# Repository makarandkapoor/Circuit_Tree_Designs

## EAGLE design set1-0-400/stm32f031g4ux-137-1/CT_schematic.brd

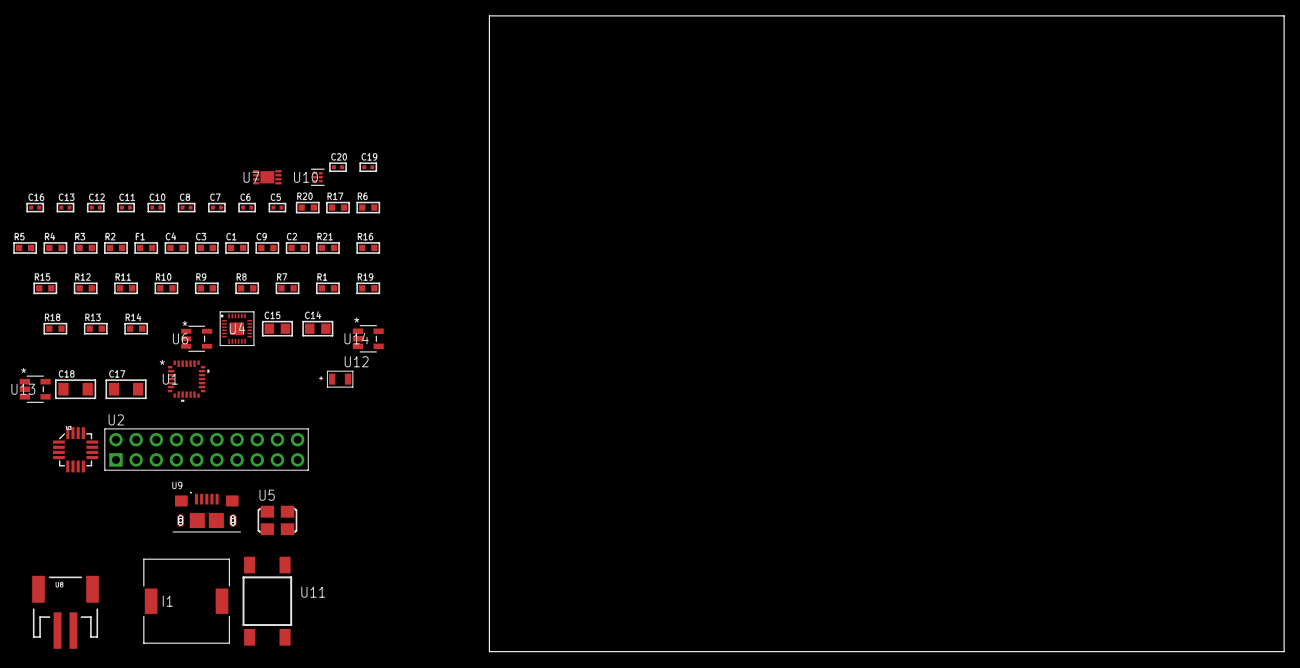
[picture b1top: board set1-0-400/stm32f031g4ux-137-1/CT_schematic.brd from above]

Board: 2 copper layers, 57 parts (0 on the bottom side), 34 nets, no tracks yet.

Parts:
C1: 1e-07; C0603
C2: 4.7e-06; C0603
C3: 1e-08; C0603
C4: 1e-06; C0603
C5, C10, C11, C16: 1e-07; C0402
C6, C7, C8, C12, C13, C19, C20: 1e-08; C0402
C9: 4.7e-07; C0603
C14, C15: 1e-05; C0805
C17, C18: 1e-05; C1206
F1: 240.0; L0603
I1: 2.5e-06; DR1040
R1, R7, R8, R9, R10, R11, R12, R15, R16, R21: 10000.0; R0603
R2: 1000.0; R0603
R3: 1600.5; R0603
R4: 4700.0; R0603
R5, R6: 2200.0; R0603
R13: 220000.0; R0603
R14: 1000000.0; R0603
R17: 9100.0; R0603
R18: 680000.0; R0603
R19: 120000.0; R0603
R20: 2000.0; R0603
U1: stm32f031g4u7; UFQFPN28
U2: TST-110-05-T-D-RA
U3: l3g4200d; LGA-16
U4: MPU-9250; QFN24_2
U5: ASFL1-25MHZ-NCS; ASFL1
U6: ltc3406es5; TSOT-23-5
U7: MCP73831T-2ACI/MC; DFN8_2X3MC
U8: S2B-PH-SM4-TB(LF)(SN); JST-2-SMD
U9: 10118193-0001LF; FCI_10118193-0001LF
U10: TPS3895ADRYR; SON-6
U11: 4-1437565-2; SW_4-1437565-2
U12: Q65110A2395; LGM67K-G1J2-24-Z
U13, U14: nc7sz125m5x; NC7SZ125M5X

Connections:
CLK_U1_2: U1.2, U5.3
GND: C1.2, C2.2, C3.2, C4.2, C5.2, C6.2, C7.2, C8.2, C10.2, C11.2, C12.2, C13.2, C14.2, C15.1, C15.2, C16.2, C17.2, C18.2, C19.2, C20.2, R2.2, R7.2, R9.1, R9.2, R12.2, R13.2, R17.2, R19.2, R20.2, U1.16, U2.4, U2.6, U2.8, U2.10, U2.12, U2.14, U2.16, U2.18, U2.20, U3.8, U3.9, U3.10, U3.11, U3.12, U3.13, U4.18, U4.20, U4.25, U5.2, U6.2, U7.6, U7.9, U8.2, U9.5, U9.6, U9.7, U9.8, U9.9, U10.2, U12.C, U13.2, U13.3, U14.1, U14.3
INPUT_USBPOWER_5V: C17.1, R21.2, U7.1, U7.2, U9.1
NET_U1_1: R7.1, U1.1
NET_U1_4: R4.1, U1.4, U14.4
NET_U1_5: C3.1, C4.1, F1.1, U1.5
NET_U1_19: R5.1, U1.19, U4.23
NET_U1_20: R6.1, U1.20, U4.24
NET_U1_27: R3.1, U1.27, U12.A
NET_U1_28: R1.1, U1.28, U11.3, U11.4
NET_U3_14: C8.1, C9.1, U3.14
NET_U4_9: R12.1, U4.9
NET_U4_10: C10.1, U4.10
NET_U4_22: R11.1, U4.22
NET_U6_3: I1.1, U6.3
NET_U6_5: R13.1, R14.1, U6.5
NET_U6_ATNET_3: I1.2, R14.2
NET_U7_5: R21.1, U7.5
NET_U7_8: R20.1, U7.8
NET_U10_1: R16.1, R17.1, U10.1
NET_U10_3: R18.2, R19.1, U10.3
NET_U10_4: R15.1, U10.4, U13.4, U14.2
NET_U11_1: R2.1, U11.1, U11.2
PROC_GPIO_TO_U4_FSYNC: U1.6, U4.11
PROC_GPIO_TO_U4_INT_B: U1.3, U4.12
PROC_SPI1_MISO: U1.12, U3.4
PROC_SPI1_MOSI: U1.13, U3.3
PROC_SPI1_NSS: R10.1, U1.10, U3.5
PROC_SPI1_SCK: U1.11, U3.2
PROC_SYS_SWCLK: U1.22, U2.9
PROC_SYS_SWDIO: U1.21, U2.7
RST_OUT_U2_SRESET_B: R8.1, U2.15, U13.1
VCC_S1_3V7: C14.1, C18.1, U6.4, U7.3, U7.4, U8.1
VCC_TIER1_3V3: C1.1, C2.1, C5.1, C6.1, C7.1, C11.1, C12.1, C13.1, C15.2, C16.1, C19.1, C20.1, F1.2, I1.2, R1.2, R3.2, R4.2, R5.2, R6.2, R8.2, R10.2, R11.2, R14.2, R15.2, R16.2, R18.1, U1.17, U2.1, U3.1, U3.15, U3.16, U4.1, U4.8, U4.13, U5.4, U10.6, U13.5, U14.5

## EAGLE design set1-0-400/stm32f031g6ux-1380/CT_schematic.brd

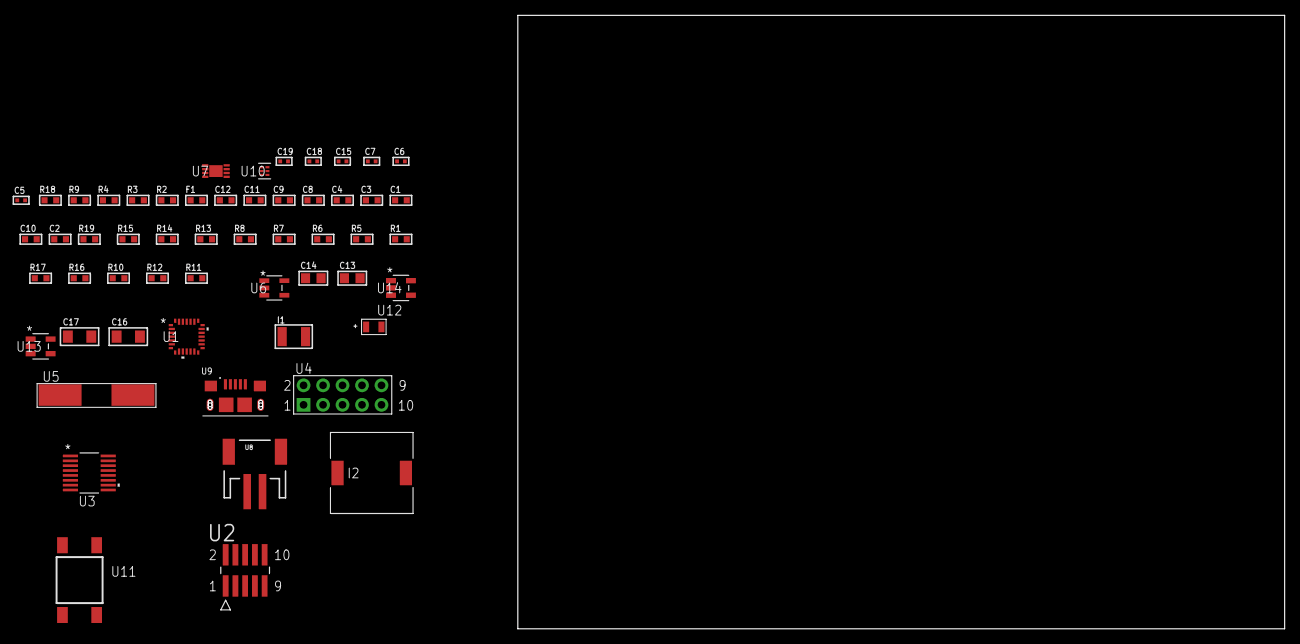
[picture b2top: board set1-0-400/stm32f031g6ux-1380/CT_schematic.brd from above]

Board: 2 copper layers, 55 parts (0 on the bottom side), 37 nets, no tracks yet.

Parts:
C1: 1e-07; C0603
C2: 4.7e-06; C0603
C3: 1e-08; C0603
C4, C8, C9, C11, C12: 1e-06; C0603
C5, C6: 1e-11; C0402
C7, C15: 1e-07; C0402
C10: 2.2e-07; C0603
C13, C14: 1e-05; C0805
C16, C17: 1e-05; C1206
C18, C19: 1e-08; C0402
F1: 240.0; L0603
I1: 1e-05; L1210
I2: 7e-06; DR1040
R1, R5, R6, R7, R8, R13, R14, R19: 10000.0; R0603
R2: 1000.0; R0603
R3: 1270.0; R0603
R4: 4700.0; R0603
R9: 5.0; R0603
R10: 100000.0; R0603
R11: 309473.68421053; R0603
R12: 1000000.0; R0603
R15: 18000.0; R0603
R16: 470000.0; R0603
R17: 120000.0; R0603
R18: 2000.0; R0603
U1: stm32f031g6u7; UFQFPN28
U2: FTSH-105-01-L-DV-K; SAMTEC_FTSH-105-01-L-DV-K
U3: LTC2804CGN-1#PBF; SSOP-16
U4: HTSS-105-01-G-D
U5: ABLS-25.000MHZ-B2F-T
U6: ltc3406es5; TSOT-23-5
U7: MCP73831T-2ACI/MC; DFN8_2X3MC
U8: S2B-PH-SM4-TB(LF)(SN); JST-2-SMD
U9: 10118193-0001LF; FCI_10118193-0001LF
U10: TPS3895ADRYR; SON-6
U11: 4-1437565-2; SW_4-1437565-2
U12: Q65110A2395; LGM67K-G1J2-24-Z
U13, U14: nc7sz125m5x; NC7SZ125M5X

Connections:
CLK_CRYSTAL_U1_2: C5.1, U1.2, U5.1
CLK_CRYSTAL_U1_3: C6.1, U1.3, U5.2
GND: C1.2, C2.2, C3.2, C4.2, C5.2, C6.2, C7.2, C8.2, C9.2, C11.2, C12.2, C13.2, C14.1, C14.2, C15.2, C16.2, C17.2, C18.2, C19.2, R2.2, R5.2, R9.2, R11.2, R15.2, R17.2, R18.2, U1.16, U2.3, U2.5, U3.8, U4.9, U6.2, U7.6, U7.9, U8.2, U9.5, U9.6, U9.7, U9.8, U9.9, U10.2, U12.C, U13.2, U13.3, U14.1, U14.3
INPUT_USBPOWER_5V: C16.1, R19.2, U7.1, U7.2, U9.1
NET_U1_1: R5.1, U1.1
NET_U1_4: R4.1, U1.4, U14.4
NET_U1_5: C3.1, C4.1, F1.1, U1.5
NET_U1_27: R3.1, U1.27, U12.A
NET_U1_28: R1.1, U1.28, U11.3, U11.4
NET_U2_9: R9.1, U2.9
NET_U3_6: C8.1, U3.6
NET_U3_7: C10.1, I1.2, U3.7
NET_U3_9: C9.1, U3.9
NET_U3_10: C10.2, U3.10
NET_U3_11: R10.1, U3.11
NET_U4_3: U3.1, U4.3
NET_U4_4: U3.2, U4.4
NET_U4_5: U3.3, U4.5
NET_U4_6: U3.4, U4.6
NET_U6_3: I2.1, U6.3
NET_U6_5: R11.1, R12.1, U6.5
NET_U6_ATNET_3: I2.2, R12.2
NET_U7_5: R19.1, U7.5
NET_U7_8: R18.1, U7.8
NET_U10_1: R14.1, R15.1, U10.1
NET_U10_3: R16.2, R17.1, U10.3
NET_U10_4: R13.1, U10.4, U13.4, U14.2
NET_U11_1: R2.1, U11.1, U11.2
PROC_SYS_SWCLK: R7.1, U1.22, U2.4
PROC_SYS_SWDIO: R8.1, U1.21, U2.2
PROC_USART1_CTS: U1.6, U3.13
PROC_USART1_RTS: U1.7, U3.15
PROC_USART1_RX: U1.9, U3.16
PROC_USART1_TX: U1.8, U3.14
RST_OUT_U2_JTAG_RST_B: R6.1, U2.10, U13.1
VCC_S1_3V7: C13.1, C17.1, U6.4, U7.3, U7.4, U8.1
VCC_TIER1_2V5: C1.1, C2.1, C7.1, C11.1, C12.1, C14.2, C15.1, C18.1, C19.1, F1.2, I1.1, I2.2, R1.2, R3.2, R4.2, R6.2, R7.2, R8.2, R10.2, R12.2, R13.2, R14.2, R16.1, U1.17, U2.1, U3.5, U3.12, U10.6, U13.5, U14.5

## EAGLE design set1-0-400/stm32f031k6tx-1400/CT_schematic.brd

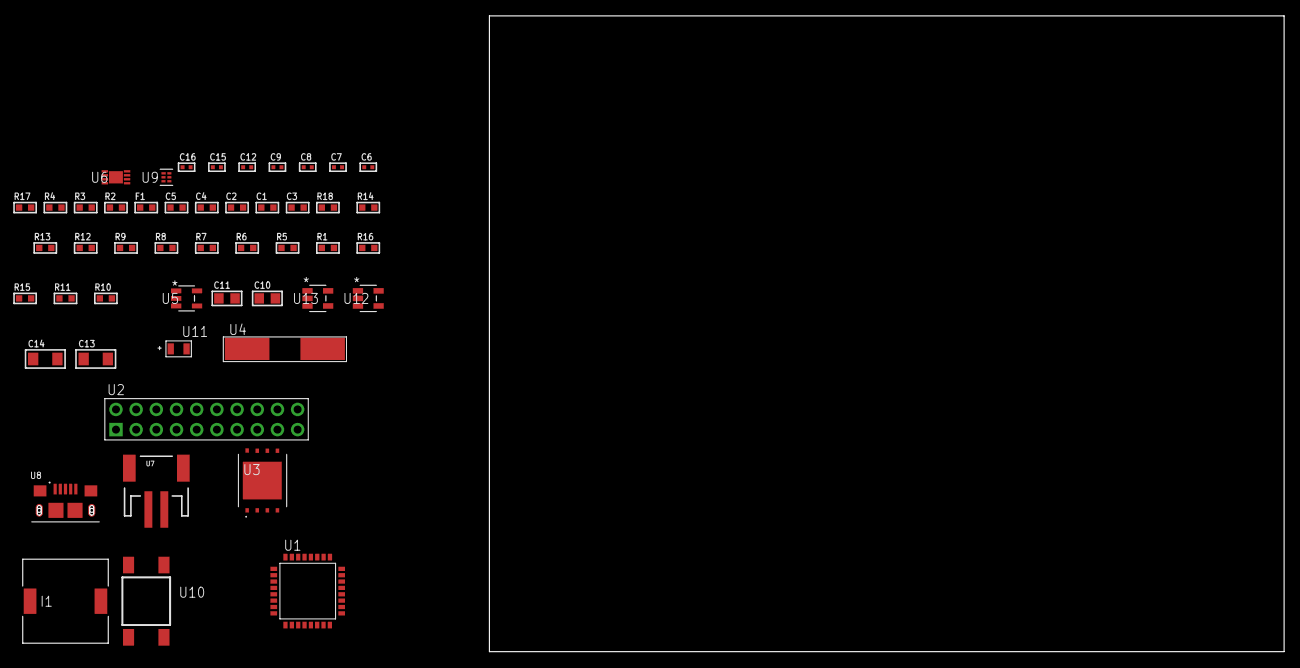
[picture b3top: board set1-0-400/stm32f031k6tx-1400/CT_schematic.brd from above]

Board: 2 copper layers, 156.9 x 80.0 mm, 49 parts (0 on the bottom side), 29 nets, no tracks yet.

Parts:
C1, C2: 1e-07; C0603
C3: 4.7e-06; C0603
C4: 1e-08; C0603
C5: 1e-06; C0603
C6, C7: 1e-11; C0402
C8, C12: 1e-07; C0402
C9, C15, C16: 1e-08; C0402
C10, C11: 1e-05; C0805
C13, C14: 1e-05; C1206
F1: 240.0; L0603
I1: 7e-06; DR1040
R1, R5, R6, R7, R8, R9, R12, R13, R18: 10000.0; R0603
R2: 1000.0; R0603
R3: 1270.0; R0603
R4: 4700.0; R0603
R10: 309473.68421053; R0603
R11: 1000000.0; R0603
R14: 18000.0; R0603
R15: 470000.0; R0603
R16: 120000.0; R0603
R17: 2000.0; R0603
U1: stm32f031k6t6; LQFP32
U2: TST-110-05-T-D-RA
U3: S25FL128SDPNFI001; WNG008
U4: ABLS-25.000MHZ-B2F-T
U5: ltc3406es5; TSOT-23-5
U6: MCP73831T-2ACI/MC; DFN8_2X3MC
U7: S2B-PH-SM4-TB(LF)(SN); JST-2-SMD
U8: 10118193-0001LF; FCI_10118193-0001LF
U9: TPS3895ADRYR; SON-6
U10: 4-1437565-2; SW_4-1437565-2
U11: Q65110A2395; LGM67K-G1J2-24-Z
U12, U13: nc7sz125m5x; NC7SZ125M5X

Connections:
CLK_CRYSTAL_U1_2: C6.1, U1.2, U4.1
CLK_CRYSTAL_U1_3: C7.1, U1.3, U4.2
GND: C1.2, C2.2, C3.2, C4.2, C5.2, C6.2, C7.2, C8.2, C9.2, C10.2, C11.1, C11.2, C12.2, C13.2, C14.2, C15.2, C16.2, R2.2, R5.2, R10.2, R14.2, R16.2, R17.2, U1.16, U1.32, U2.4, U2.6, U2.8, U2.10, U2.12, U2.14, U2.16, U2.18, U2.20, U3.4, U3.PAD, U5.2, U6.6, U6.9, U7.2, U8.5, U8.6, U8.7, U8.8, U8.9, U9.2, U11.C, U12.2, U12.3, U13.1, U13.3
INPUT_USBPOWER_5V: C13.1, R18.2, U6.1, U6.2, U8.1
NET_U1_4: R4.1, U1.4, U13.4
NET_U1_5: C4.1, C5.1, F1.1, U1.5
NET_U1_29: R3.1, U1.29, U11.A
NET_U1_30: R1.1, U1.30, U10.3, U10.4
NET_U1_31: R5.1, U1.31
NET_U3_3: R7.1, U3.3
NET_U3_7: R9.1, U3.7
NET_U5_3: I1.1, U5.3
NET_U5_5: R10.1, R11.1, U5.5
NET_U5_ATNET_3: I1.2, R11.2
NET_U6_5: R18.1, U6.5
NET_U6_8: R17.1, U6.8
NET_U9_1: R13.1, R14.1, U9.1
NET_U9_3: R15.2, R16.1, U9.3
NET_U9_4: R12.1, U9.4, U12.4, U13.2
NET_U10_1: R2.1, U10.1, U10.2
PROC_SPI1_MISO: U1.12, U3.2
PROC_SPI1_MOSI: U1.13, U3.5
PROC_SPI1_NSS: R8.1, U1.10, U3.1
PROC_SPI1_SCK: U1.11, U3.6
PROC_SYS_SWCLK: U1.24, U2.9
PROC_SYS_SWDIO: U1.23, U2.7
RST_OUT_U2_SRESET_B: R6.1, U2.15, U12.1
VCC_S1_3V7: C10.1, C14.1, U5.4, U6.3, U6.4, U7.1
VCC_TIER1_2V5: C1.1, C2.1, C3.1, C8.1, C9.1, C11.2, C12.1, C15.1, C16.1, F1.2, I1.2, R1.2, R3.2, R4.2, R6.2, R7.2, R8.2, R9.2, R11.2, R12.2, R13.2, R15.1, U1.1, U1.17, U2.1, U3.8, U9.6, U12.5, U13.5

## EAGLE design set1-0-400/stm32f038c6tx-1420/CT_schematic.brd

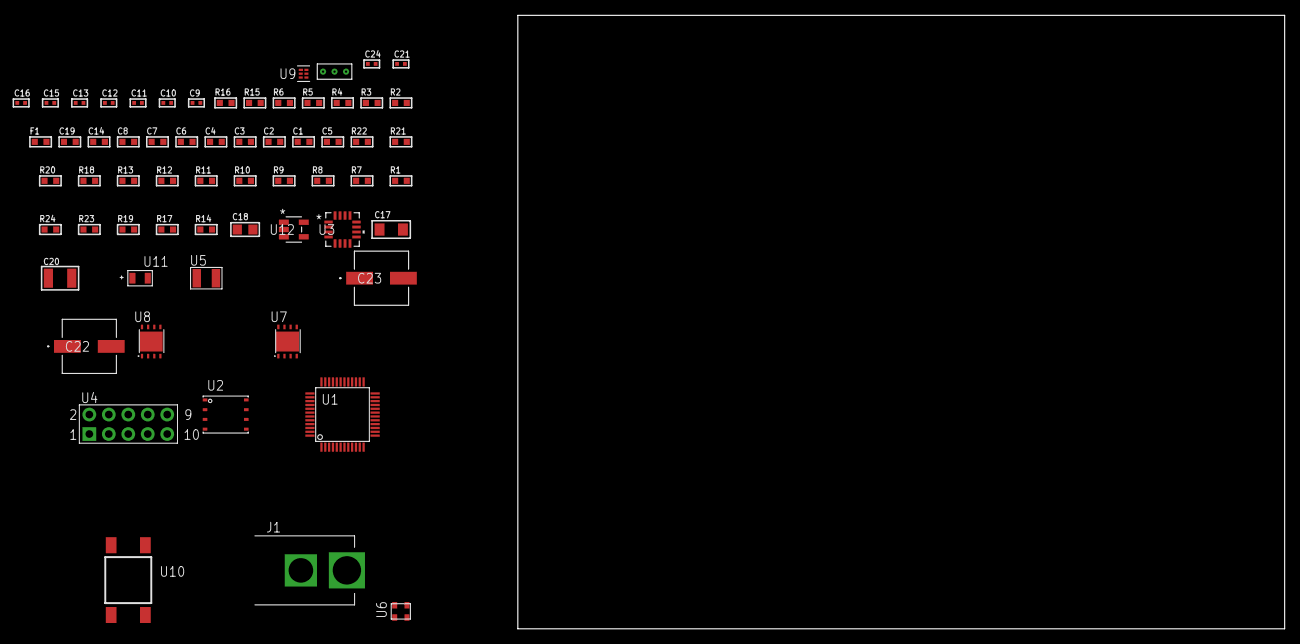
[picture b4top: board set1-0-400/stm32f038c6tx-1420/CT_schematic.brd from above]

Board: 2 copper layers, 100.0 x 80.0 mm, 63 parts (0 on the bottom side), 38 nets, no tracks yet.

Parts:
C1, C8, C14, C19: 1e-06; C0603
C2, C3, C4, C6: 1e-07; C0603
C5: 4.7e-06; C0603
C7: 1e-08; C0603
C9, C10: 1e-11; C0402
C11, C15, C16, C24: 1e-08; C0402
C12, C13, C21: 1e-07; C0402
C17: 1e-05; C1206
C18: 1e-05; C0805
C20: 1e-05; C1210
C22, C23: 0.0001; EXV-9H
F1: 240.0; L0603
J1: PJ-037B; PJ-037B_PACKAGE
R1, R7, R8, R9, R10, R11, R12, R13, R20, R21: 10000.0; R0603
R2, R16: 1000.0; R0603
R3: 910.0; R0603
R4: 4700.0; R0603
R5, R6: 2200.0; R0603
R14, R17, R19: 100000.0; R0603
R15: 806.0; R0603
R18: 68000.0; R0603
R22: 82000.0; R0603
R23: 300000.0; R0603
R24: 120000.0; R0603
U1: stm32f038c6t7; LQFP48
U2: 24AA256-I/MF; DFN8-S
U3: TSC2046IRGVR; VQFN-16
U4: HTSS-105-01-G-D
U5: ABS07-32.768KHZ-7-T
U6: ASDMB-25.000MHZ-EC-T; ASDMB-XX.XXXXMHZ-XX-XX-XXX
U7: LP3878SDX-ADJ/NOPB; WSON-8
U8: LP2951ACSDX/NOPB; WSON-8
U9: TPS3895ADRYR; SON-6
U10: 4-1437565-2; SW_4-1437565-2
U11: Q65110A2395; LGM67K-G1J2-24-Z
U12: nc7sz125m5x; NC7SZ125M5X
U13: Dummy; DUMMY_PACKAGE_133

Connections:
CLK_CRYSTAL_U1_3: C9.1, U1.3, U5.1
CLK_CRYSTAL_U1_4: C10.1, U1.4, U5.2
CLK_U1_5: U1.5, U6.3
GND: C1.2, C2.2, C3.2, C4.2, C5.2, C6.2, C7.2, C8.2, C9.2, C10.2, C11.2, C12.2, C13.2, C14.2, C15.2, C16.2, C17.2, C18.2, C19.2, C20.2, C21.2, C22.2, C23.2, C24.2, J1.2, R2.2, R7.2, R8.2, R16.2, R19.2, R22.2, R24.2, U1.8, U1.23, U1.47, U2.4, U3.10, U4.9, U6.2, U7.3, U7.PAD, U8.3, U8.4, U8.PAD, U9.2, U11.C, U12.1, U12.3, U13.1
NET_U1_7: R4.1, U1.7, U12.4
NET_U1_9: C7.1, C8.1, F1.1, U1.9
NET_U1_20: R8.1, U1.20
NET_U1_21: R5.1, U1.21, U2.6
NET_U1_22: R6.1, U1.22, U2.5
NET_U1_44: R7.1, U1.44
NET_U1_45: R3.1, U1.45, U11.A
NET_U1_46: R1.1, U1.46, U10.3, U10.4
NET_U2_1: R9.1, U2.1
NET_U2_2: R10.1, U2.2
NET_U2_3: R11.1, U2.3
NET_U3_15: R13.1, U3.15
NET_U4_3: U3.7, U4.3
NET_U4_4: U3.9, U4.4
NET_U4_5: U3.6, U4.5
NET_U4_6: U3.8, U4.6
NET_U7_1: C16.1, U7.1
NET_U7_6: R15.2, R16.1, U7.6
NET_U7_8: R14.1, U7.8
NET_U8_5: R17.1, U8.5
NET_U8_7: R18.2, R19.1, U8.7
NET_U9_1: R21.1, R22.1, U9.1
NET_U9_3: R23.2, R24.1, U9.3
NET_U9_4: R20.1, U9.4, U12.2
NET_U10_1: R2.1, U10.1, U10.2
PROC_SPI1_MISO: U1.16, U3.16
PROC_SPI1_MOSI: U1.17, U3.2
PROC_SPI1_NSS: R12.1, U1.14, U3.3
PROC_SPI1_SCK: U1.15, U3.4
PROC_TIM1_CH3N: U1.19, U13.3
PROC_TIM1_CH4: U1.32, U13.2
VCC_S1_7V3: C17.1, C19.1, C22.1, C23.1, J1.1, R14.2, U7.4, U8.8
VCC_TIER1_1V8: C1.1, C2.1, C3.1, C4.1, C5.1, C6.1, C11.1, C12.1, C15.1, C18.1, C21.1, C24.1, F1.2, R1.2, R3.2, R4.2, R5.2, R6.2, R9.2, R10.2, R11.2, R12.2, R13.2, R15.1, R20.2, R21.2, R23.1, U1.1, U1.24, U1.48, U2.7, U2.8, U3.14, U6.4, U7.5, U9.6, U12.5
VCC_TIER1_2V2: C13.1, C14.1, C20.1, R17.2, R18.1, U3.5, U8.1

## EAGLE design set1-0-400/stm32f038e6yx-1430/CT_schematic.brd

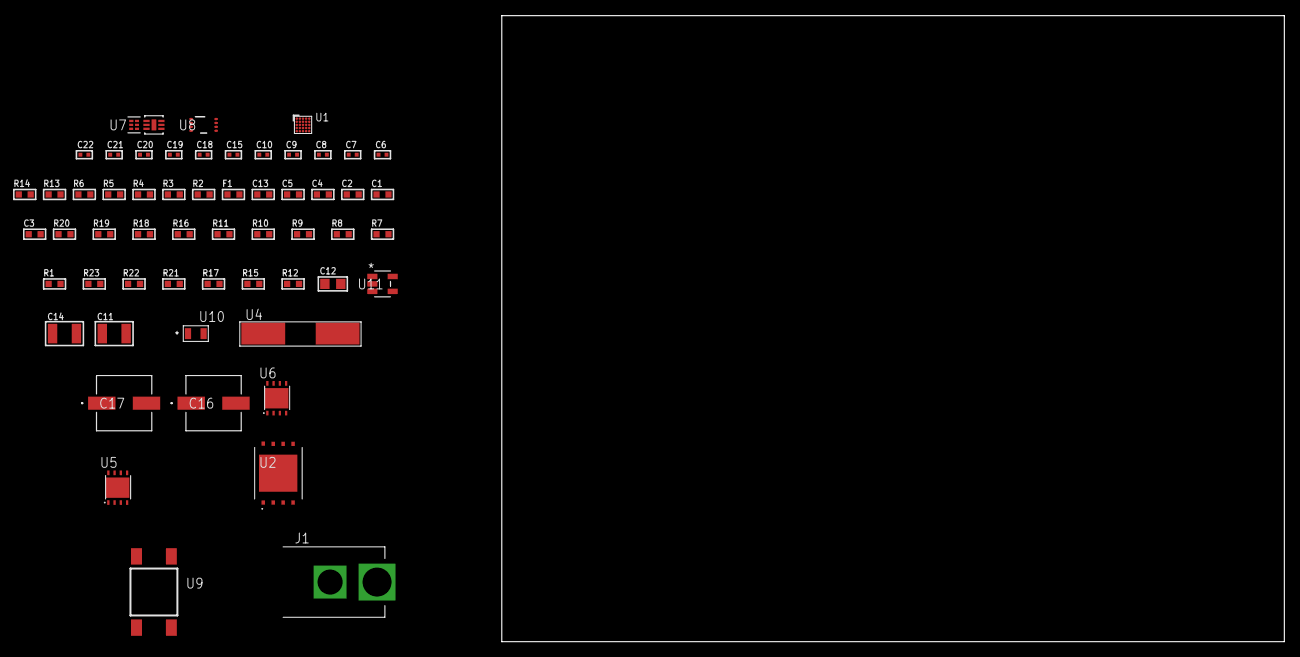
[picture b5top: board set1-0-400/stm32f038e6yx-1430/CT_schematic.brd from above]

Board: 2 copper layers, 100.0 x 80.0 mm, 58 parts (0 on the bottom side), 32 nets, no tracks yet.

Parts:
C1, C2: 1e-07; C0603
C3: 4.7e-06; C0603
C4: 1e-08; C0603
C5: 1e-06; C0603
C6, C7: 1e-11; C0402
C8, C10, C18, C20, C22: 1e-08; C0402
C9, C15, C19, C21: 1e-07; C0402
C11, C14: 1e-05; C1210
C12: 1e-05; C0805
C13: 8e-07; R0603
C16, C17: 0.0001; EXV-9H
F1: 240.0; L0603
J1: PJ-037B; PJ-037B_PACKAGE
R1, R7, R8, R9, R10, R11, R18, R19: 10000.0; R0603
R2, R14: 1000.0; R0603
R3: 910.0; R0603
R4: 4700.0; R0603
R5, R6: 2200.0; R0603
R12, R15, R17: 100000.0; R0603
R13: 806.0; R0603
R16: 91000.0; R0603
R20: 82000.0; R0603
R21: 300000.0; R0603
R22: 120000.0; R0603
R23: 200000.0; R0603
U1: stm32f038e6y7; WLCSP25
U2: S25FL128SDPNFI001; WNG008
U3: SI7006-A20-IM; DFN-6
U4: ABLS-25.000MHZ-B2F-T
U5: LP3878SDX-ADJ/NOPB; WSON-8
U6: LP2951ACSDX/NOPB; WSON-8
U7: TPS3895ADRYR; SON-6
U8: LSF0102DCTR; DCU0008A_N
U9: 4-1437565-2; SW_4-1437565-2
U10: Q65110A2395; LGM67K-G1J2-24-Z
U11: nc7sz125m5x; NC7SZ125M5X

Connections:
CLK_CRYSTAL_U1_A5: C6.1, U1.A5, U4.1
CLK_CRYSTAL_U1_B5: C7.1, U1.B5, U4.2
GND: C1.2, C2.2, C3.2, C4.2, C5.2, C6.2, C7.2, C8.2, C9.2, C10.2, C11.2, C12.2, C13.2, C14.2, C15.2, C16.2, C17.2, C18.2, C19.2, C20.2, C21.2, C22.2, J1.2, R2.2, R7.2, R8.2, R14.2, R17.2, R20.2, R22.2, U1.E1, U2.4, U2.PAD, U3.2, U3.7, U5.3, U5.PAD, U6.3, U6.4, U6.PAD, U7.2, U8.1, U10.C, U11.1, U11.3
NET_U1_A3: R6.1, U1.A3, U8.3
NET_U1_A4: R7.1, U1.A4
NET_U1_B2: R5.1, U1.B2, U8.4
NET_U1_C5: R4.1, U1.C5, U11.4
NET_U1_D5: C4.1, C5.1, F1.1, U1.D5
NET_U1_E2: R8.1, U1.E2
NET_U1_E4: R3.1, U1.E4, U10.A
NET_U1_E5: R1.1, U1.E5, U9.3, U9.4
NET_U2_3: R9.1, U2.3
NET_U2_7: R11.1, U2.7
NET_U5_1: C10.1, U5.1
NET_U5_6: R13.2, R14.1, U5.6
NET_U5_8: R12.1, U5.8
NET_U6_5: R15.1, U6.5
NET_U6_7: R16.2, R17.1, U6.7
NET_U7_1: R19.1, R20.1, U7.1
NET_U7_3: R21.2, R22.1, U7.3
NET_U7_4: R18.1, U7.4, U11.2
NET_U8_8: R23.1, U8.8
NET_U9_1: R2.1, U9.1, U9.2
PROC_I2C1_SCL_TOXCVR: U3.6, U8.5
PROC_I2C1_SDA_TOXCVR: U3.1, U8.6
PROC_SPI1_MISO: U1.D3, U2.2
PROC_SPI1_MOSI: U1.C2, U2.5
PROC_SPI1_NSS: R10.1, U1.B3, U2.1
PROC_SPI1_SCK: U1.C3, U2.6
VCC_S1_13V0: C11.1, C13.1, C16.1, C17.1, J1.1, R12.2, U5.4, U6.8
VCC_TIER1_1V8: C1.1, C2.1, C3.1, C8.1, C12.1, C15.1, C20.1, C21.1, C22.1, F1.2, R1.2, R3.2, R4.2, R5.2, R6.2, R9.2, R10.2, R11.2, R13.1, R18.2, R19.2, R21.1, U1.D1, U2.8, U5.5, U7.6, U8.2, U11.5
VCC_TIER1_2V5: C9.1, C14.1, C18.1, C19.1, R15.2, R16.1, R23.2, U3.5, U6.1, U8.7

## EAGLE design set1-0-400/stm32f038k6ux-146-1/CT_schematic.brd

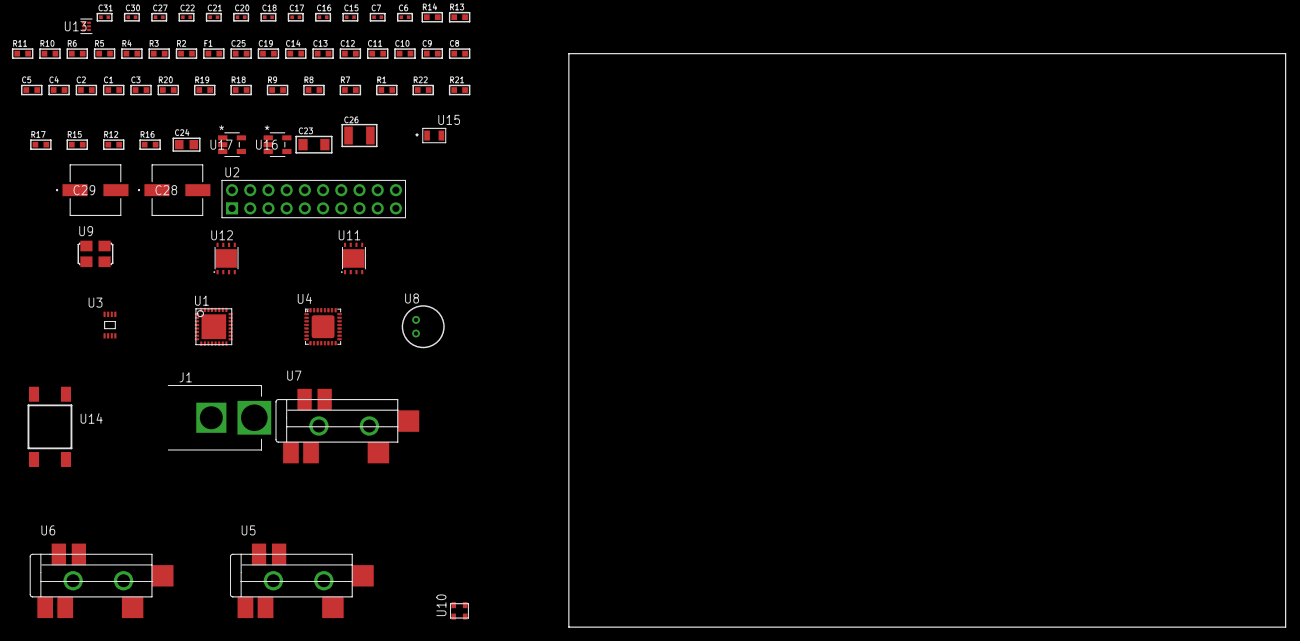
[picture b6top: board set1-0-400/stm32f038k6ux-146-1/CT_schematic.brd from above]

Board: 2 copper layers, 100.0 x 80.0 mm, 72 parts (0 on the bottom side), 42 nets, no tracks yet.

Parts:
C1, C2: 1e-07; C0603
C3: 4.7e-06; C0603
C4: 1e-08; C0603
C5, C8, C9, C10, C11, C12, C13, C14, C19, C25: 1e-06; C0603
C6, C15, C16, C17, C18, C27: 1e-07; C0402
C7, C20, C21, C22, C30, C31: 1e-08; C0402
C23: 1e-05; C1206
C24: 1e-05; C0805
C26: 1e-05; C1210
C28, C29: 0.0001; EXV-9H
F1: 240.0; L0603
J1: PJ-037B; PJ-037B_PACKAGE
R1, R7, R8, R9, R18, R19: 10000.0; R0603
R2, R14: 1000.0; R0603
R3: 910.0; R0603
R4: 4700.0; R0603
R5, R6: 2200.0; R0603
R10, R11: 1270.0; R0603
R12, R15, R17: 100000.0; R0603
R13: 806.0; R0603
R16: 153694.38; R0603
R20: 82000.0; R0603
R21: 300000.0; R0603
R22: 120000.0; R0603
U1: stm32f038k6u6; UFQFPN32
U2: TST-110-05-T-D-RA
U3: 24AA01T-I/MNY; TDFN-8/6MM
U4: SGTL5000XNAA3; QFN-32
U5, U6, U7: SJ-43515TS-SMT-TR
U8: WM-64PCT; WM-64PC
U9: ASFL-24.57MHZ-NCS; ASFL1
U10: ASDMB-25.000MHZ-EC-T; ASDMB-XX.XXXXMHZ-XX-XX-XXX
U11: LP3878SDX-ADJ/NOPB; WSON-8
U12: LP2951ACSDX/NOPB; WSON-8
U13: TPS3895ADRYR; SON-6
U14: 4-1437565-2; SW_4-1437565-2
U15: Q65110A2395; LGM67K-G1J2-24-Z
U16, U17: nc7sz125m5x; NC7SZ125M5X

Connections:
CLK_U1_2: U1.2, U10.3
CLK_U4_21: U4.21, U9.3
GND: C1.2, C2.2, C3.2, C4.2, C5.2, C6.2, C7.2, C15.2, C16.2, C17.2, C18.2, C19.2, C20.2, C21.2, C22.2, C23.2, C24.2, C25.2, C26.2, C27.2, C28.2, C29.2, C30.2, C31.2, J1.2, R2.2, R7.2, R8.2, R11.2, R14.2, R17.2, R20.2, R22.2, U1.EPAD, U2.4, U2.6, U2.8, U2.10, U2.12, U2.14, U2.16, U2.18, U2.20, U3.4, U3.7, U4.1, U4.3, U4.7, U4.EXP, U6.1, U7.1, U8.2, U9.2, U10.2, U11.3, U11.PAD, U12.3, U12.4, U12.PAD, U13.2, U15.C, U16.2, U16.3, U17.1, U17.3
NET_U1_4: R4.1, U1.4, U17.4
NET_U1_5: C4.1, C5.1, F1.1, U1.5
NET_U1_16: R8.1, U1.16
NET_U1_19: R5.1, U1.19, U3.6
NET_U1_20: R6.1, U1.20, U3.5
NET_U1_30: R3.1, U1.30, U15.A
NET_U1_31: R7.1, U1.31
NET_U1_32: R1.1, U1.32, U14.3, U14.4
NET_U4_10: C18.1, U4.10
NET_U4_29: R10.1, U4.29
NET_U4_31: R11.1, U4.31
NET_U5_1: U4.4, U5.1
NET_U5_2: U4.2, U5.2
NET_U5_5: U4.6, U5.5
NET_U6_2: C9.1, U6.2
NET_U6_5: C8.1, U6.5
NET_U7_2: C11.1, C12.1, U7.2
NET_U7_5: C10.1, U7.5
NET_U7_13: C11.2, C12.2
NET_U8_1: C13.1, C14.1, C19.1, U4.16, U8.1
NET_U8_15: C13.2, C14.2
NET_U11_1: C22.1, U11.1
NET_U11_6: R13.2, R14.1, U11.6
NET_U11_8: R12.1, U11.8
NET_U12_5: R15.1, U12.5
NET_U12_7: R16.2, R17.1, U12.7
NET_U13_1: R19.1, R20.1, U13.1
NET_U13_3: R21.2, R22.1, U13.3
NET_U13_4: R18.1, U13.4, U16.4, U17.2
NET_U14_1: R2.1, U14.1, U14.2
PROC_I2S1_CK: U1.11, U4.24
PROC_I2S1_SD: U1.13, U4.26
PROC_I2S1_WS: U1.10, U4.23
PROC_SYS_SWCLK: U1.24, U2.9
PROC_SYS_SWDIO: U1.23, U2.7
RST_OUT_U2_SRESET_B: R9.1, U2.15, U16.1
VCC_S1_7V6: C23.1, C25.1, C28.1, C29.1, J1.1, R12.2, U11.4, U12.8
VCC_TIER1_1V8: C1.1, C2.1, C3.1, C6.1, C7.1, C15.1, C16.1, C17.1, C21.1, C24.1, C27.1, C30.1, C31.1, F1.2, R1.2, R3.2, R4.2, R5.2, R6.2, R9.2, R10.2, R13.1, R18.2, R19.2, R21.1, U1.1, U1.17, U2.1, U3.8, U4.5, U4.20, U4.30, U10.4, U11.5, U13.6, U16.5, U17.5
VCC_TIER1_3V3: C20.1, C26.1, R15.2, R16.1, U9.4, U12.1

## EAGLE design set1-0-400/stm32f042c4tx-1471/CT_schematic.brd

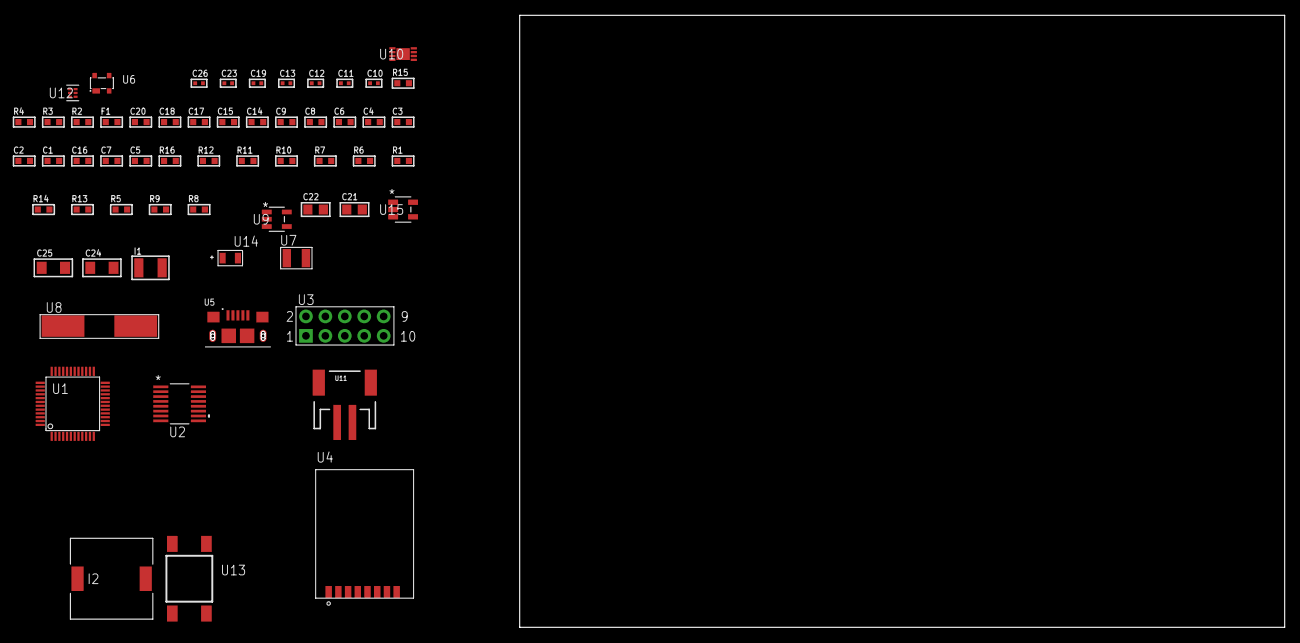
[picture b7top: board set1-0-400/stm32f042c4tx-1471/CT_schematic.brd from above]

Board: 2 copper layers, 60 parts (0 on the bottom side), 41 nets, no tracks yet.

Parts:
C1, C9, C14, C15, C17, C18, C20: 1e-06; C0603
C2, C3, C4, C6: 1e-07; C0603
C5, C7: 4.7e-06; C0603
C8: 1e-08; C0603
C10, C11, C12, C13: 1e-11; C0402
C16: 2.2e-07; C0603
C19, C23: 1e-07; C0402
C21, C22: 1e-05; C0805
C24, C25: 1e-05; C1206
C26: 1e-08; C0402
F1: 240.0; L0603
I1: 1e-05; L1210
I2: 5.2e-06; DR1040
R1, R6, R7, R10, R11, R16: 10000.0; R0603
R2: 1000.0; R0603
R3: 1270.0; R0603
R4: 4700.0; R0603
R5: 100000.0; R0603
R8: 309473.68421053; R0603
R9: 1000000.0; R0603
R12: 18000.0; R0603
R13: 470000.0; R0603
R14: 120000.0; R0603
R15: 2000.0; R0603
U1: stm32f042c4t6; LQFP48
U2: LTC2804CGN-1#PBF; SSOP-16
U3: HTSS-105-01-G-D
U4: RFM75-S
U5: 10118193-0001LF; FCI_10118193-0001LF
U6: prtr5v0u2ax; SOT143B
U7: ABS07-32.768KHZ-7-T
U8: ABLS-25.000MHZ-B2F-T
U9: ltc3406es5; TSOT-23-5
U10: MCP73831T-2ACI/MC; DFN8_2X3MC
U11: S2B-PH-SM4-TB(LF)(SN); JST-2-SMD
U12: TPS3895ADRYR; SON-6
U13: 4-1437565-2; SW_4-1437565-2
U14: Q65110A2395; LGM67K-G1J2-24-Z
U15: nc7sz125m5x; NC7SZ125M5X

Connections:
CLK_CRYSTAL_U1_3: C10.1, U1.3, U7.1
CLK_CRYSTAL_U1_4: C11.1, U1.4, U7.2
CLK_CRYSTAL_U1_5: C12.1, U1.5, U8.1
CLK_CRYSTAL_U1_6: C13.1, U1.6, U8.2
GND: C1.2, C2.2, C3.2, C4.2, C5.2, C6.2, C7.2, C8.2, C9.2, C10.2, C11.2, C12.2, C13.2, C14.2, C15.2, C17.2, C18.2, C19.2, C20.2, C21.2, C22.1, C22.2, C23.2, C24.2, C25.2, C26.2, R2.2, R8.2, R12.2, R14.2, R15.2, U1.8, U1.23, U1.35, U1.47, U2.8, U3.9, U4.1, U5.5, U5.6, U5.7, U5.8, U5.9, U6.1, U9.2, U10.6, U10.9, U11.2, U12.2, U14.C, U15.1, U15.3
INPUT_USBPOWER_5V: C24.1, R16.2, U5.1, U6.4, U10.1, U10.2
NET_U1_7: R4.1, U1.7, U15.4
NET_U1_9: C8.1, C9.1, F1.1, U1.9
NET_U1_45: R3.1, U1.45, U14.A
NET_U1_46: R1.1, U1.46, U13.3, U13.4
NET_U2_6: C14.1, U2.6
NET_U2_7: C16.1, I1.2, U2.7
NET_U2_9: C15.1, U2.9
NET_U2_10: C16.2, U2.10
NET_U2_11: R5.1, U2.11
NET_U3_3: U2.1, U3.3
NET_U3_4: U2.2, U3.4
NET_U3_5: U2.3, U3.5
NET_U3_6: U2.4, U3.6
NET_U4_3: R6.1, U4.3
NET_U9_3: I2.1, U9.3
NET_U9_5: R8.1, R9.1, U9.5
NET_U9_ATNET_3: I2.2, R9.2
NET_U10_5: R16.1, U10.5
NET_U10_8: R15.1, U10.8
NET_U12_1: R11.1, R12.1, U12.1
NET_U12_3: R13.2, R14.1, U12.3
NET_U12_4: R10.1, U12.4, U15.2
NET_U13_1: R2.1, U13.1, U13.2
PROC_SPI1_MISO: U1.16, U4.7
PROC_SPI1_MOSI: U1.17, U4.6
PROC_SPI1_NSS: R7.1, U1.14, U4.4
PROC_SPI1_SCK: U1.15, U4.5
PROC_USART2_CTS: U1.10, U2.13
PROC_USART2_RTS: U1.11, U2.15
PROC_USART2_RX: U1.13, U2.16
PROC_USART2_TX: U1.12, U2.14
PROC_USB_DM: U1.32, U5.2, U6.3
PROC_USB_DP: U1.33, U5.3, U6.2
VCC_S1_3V7: C21.1, C25.1, U9.4, U10.3, U10.4, U11.1
VCC_TIER1_2V5: C1.1, C2.1, C3.1, C4.1, C5.1, C6.1, C7.1, C17.1, C18.1, C19.1, C20.1, C22.2, C23.1, C26.1, F1.2, I1.1, I2.2, R1.2, R3.2, R4.2, R5.2, R6.2, R7.2, R9.2, R10.2, R11.2, R13.1, U1.1, U1.24, U1.36, U1.48, U2.5, U2.12, U4.2, U12.6, U15.5

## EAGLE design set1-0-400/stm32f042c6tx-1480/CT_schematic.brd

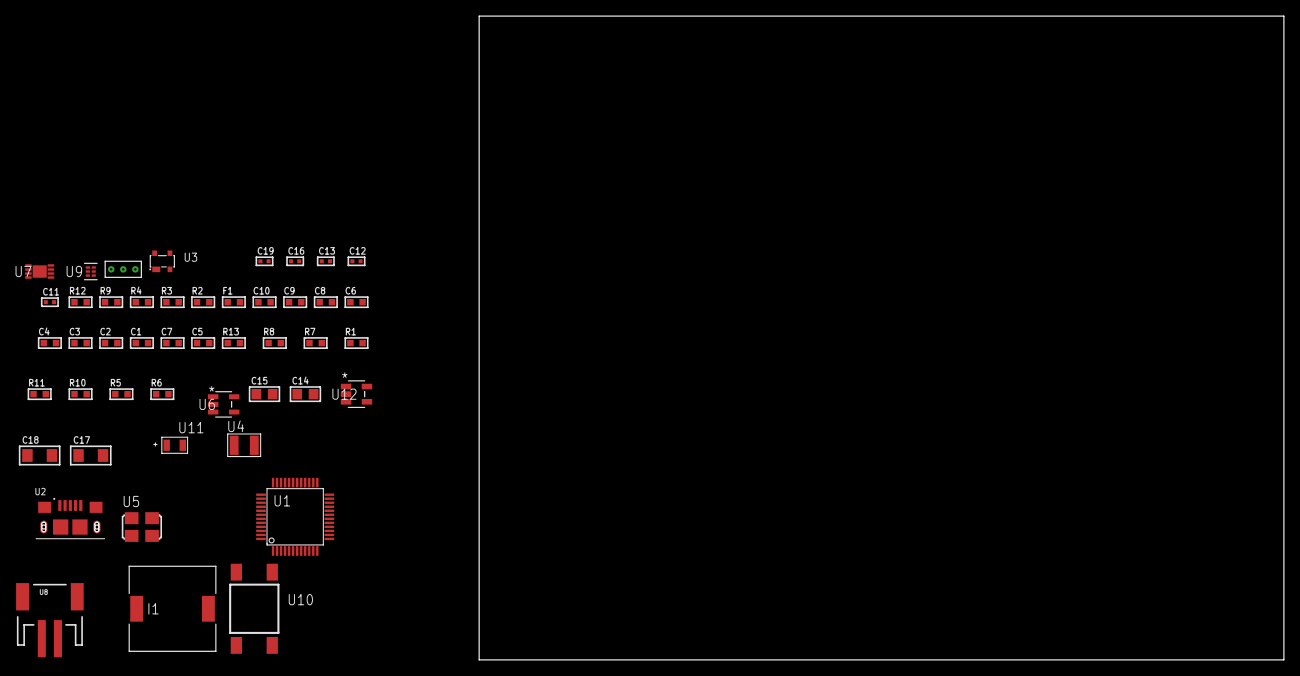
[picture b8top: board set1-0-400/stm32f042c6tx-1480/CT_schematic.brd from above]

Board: 2 copper layers, 154.3 x 80.0 mm, 47 parts (0 on the bottom side), 24 nets, no tracks yet.

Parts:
C1, C10: 1e-06; C0603
C2, C3, C4, C6, C8: 1e-07; C0603
C5, C7: 4.7e-06; C0603
C9: 1e-08; C0603
C11, C12: 1e-11; C0402
C13, C19: 1e-08; C0402
C14, C15: 1e-05; C0805
C16: 1e-07; C0402
C17, C18: 1e-05; C1206
F1: 240.0; L0603
I1: 2.5e-06; DR1040
R1, R7, R8, R13: 10000.0; R0603
R2: 1000.0; R0603
R3: 1600.5; R0603
R4: 4700.0; R0603
R5: 220000.0; R0603
R6: 1000000.0; R0603
R9: 9100.0; R0603
R10: 680000.0; R0603
R11: 120000.0; R0603
R12: 2000.0; R0603
U1: stm32f042c6t6; LQFP48
U2: 10118193-0001LF; FCI_10118193-0001LF
U3: prtr5v0u2ax; SOT143B
U4: ABS07-32.768KHZ-7-T
U5: ASFL1-25MHZ-NCS; ASFL1
U6: ltc3406es5; TSOT-23-5
U7: MCP73831T-2ACI/MC; DFN8_2X3MC
U8: S2B-PH-SM4-TB(LF)(SN); JST-2-SMD
U9: TPS3895ADRYR; SON-6
U10: 4-1437565-2; SW_4-1437565-2
U11: Q65110A2395; LGM67K-G1J2-24-Z
U12: nc7sz125m5x; NC7SZ125M5X
U13: Dummy; DUMMY_PACKAGE_96

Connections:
CLK_CRYSTAL_U1_3: C11.1, U1.3, U4.1
CLK_CRYSTAL_U1_4: C12.1, U1.4, U4.2
CLK_U1_5: U1.5, U5.3
GND: C1.2, C2.2, C3.2, C4.2, C5.2, C6.2, C7.2, C8.2, C9.2, C10.2, C11.2, C12.2, C13.2, C14.2, C15.1, C15.2, C16.2, C17.2, C18.2, C19.2, R2.2, R5.2, R9.2, R11.2, R12.2, U1.8, U1.23, U1.35, U1.47, U2.5, U2.6, U2.7, U2.8, U2.9, U3.1, U5.2, U6.2, U7.6, U7.9, U8.2, U9.2, U11.C, U12.1, U12.3, U13.1
INPUT_USBPOWER_5V: C17.1, R13.2, U2.1, U3.4, U7.1, U7.2
NET_U1_7: R4.1, U1.7, U12.4
NET_U1_9: C9.1, C10.1, F1.1, U1.9
NET_U1_45: R3.1, U1.45, U11.A
NET_U1_46: R1.1, U1.46, U10.3, U10.4
NET_U6_3: I1.1, U6.3
NET_U6_5: R5.1, R6.1, U6.5
NET_U6_ATNET_3: I1.2, R6.2
NET_U7_5: R13.1, U7.5
NET_U7_8: R12.1, U7.8
NET_U9_1: R8.1, R9.1, U9.1
NET_U9_3: R10.2, R11.1, U9.3
NET_U9_4: R7.1, U9.4, U12.2
NET_U10_1: R2.1, U10.1, U10.2
PROC_ADC_IN3: U1.13, U13.2
PROC_ADC_IN4: U1.14, U13.3
PROC_USB_DM: U1.32, U2.2, U3.3
PROC_USB_DP: U1.33, U2.3, U3.2
VCC_S1_3V7: C14.1, C18.1, U6.4, U7.3, U7.4, U8.1
VCC_TIER1_3V3: C1.1, C2.1, C3.1, C4.1, C5.1, C6.1, C7.1, C8.1, C13.1, C15.2, C16.1, C19.1, F1.2, I1.2, R1.2, R3.2, R4.2, R6.2, R7.2, R8.2, R10.1, U1.1, U1.24, U1.36, U1.48, U5.4, U9.6, U12.5

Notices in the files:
parts and their libraries:
circuit_tree: (C) 2014 Tomasz Boleslaw CEDRO, cederom@tlen.pl, http://www.tomek.cedro.info.
